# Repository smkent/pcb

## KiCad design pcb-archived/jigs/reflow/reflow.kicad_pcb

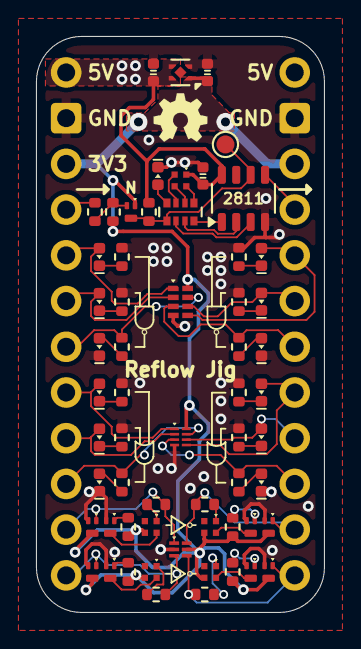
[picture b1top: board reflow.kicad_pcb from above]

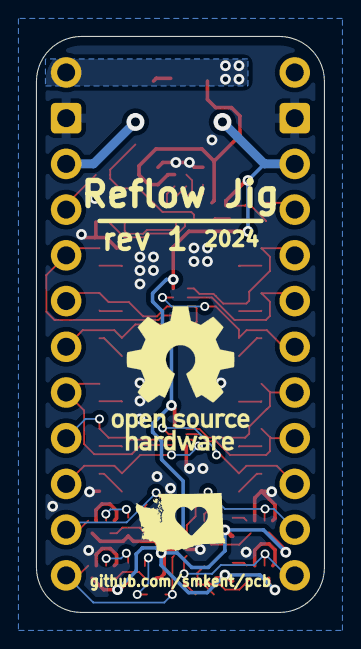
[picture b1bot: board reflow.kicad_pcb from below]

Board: 2 copper layers, 16.0 x 32.0 mm, 62 parts (2 on the bottom side), 54 nets.

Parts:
C0, C1, C2: 10u; C_0402_1005Metric
D1, D2, D3, D4, D5, D6, D7, D8, D9, D10, D11, D12, D13: Green; LED_0402_1005Metric
J1, J2: Pin headers; PinHeader_1x12_P2.54mm_Vertical_simple_pad2gnd
LED1, LED2, LED3, LED4, LED5: XL-B1010RGBT-HF; LED_RGB_XL-B1010RGBT-HF_1.0x1.0mm
Q1, Q2, Q3, Q4, Q5, Q6, Q7, Q8, Q9: SDV301N3; DFN1006-3
R1: 100R; R_0402_1005Metric
R2, R3, R4, R5, R6, R7: 10K; R_0402_1005Metric
R8, R9, R10, R11, R12, R13, R14, R15, R16, R17, R18, R19, R20, R21, R22, R23: 5K1; R_0402_1005Metric
RN1: 5K1; R_Array_Convex_4x0402
TP1: TestPoint; TestPoint_Pad_D1.0mm
U1: WS2811F; FSOP-8_3.3x1.7mm_P0.80mm
U2: 74LVC2G00HD4-7; X2-DFN2010-8_L2.0-W1.0-P0.50-BL
U3: 74LVC2G32RA3-7; X2-DFN1210-8_L1.2-W1.0-P0.30-BL
U4: 74AUP2G06FW4-7; X2-DFN1010-6_L1.0-W1.0-P0.35-BL
U5: ME6211C33U4; UDFN-4-1EP_1x1mm_P0.65mm_EP0.48x0.48mm

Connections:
+3V3: C1.1, J1.3, J2.3, LED2.3 (GK), LED3.3 (GK), LED4.3 (GK), LED5.3 (GK), Q1.1 (G), Q2.3 (D), Q4.3 (D), Q7.3 (D), Q8.3 (D), R2.2, R4.1, R5.2, R6.1, R7.2, U2.8 (V_{CC}), U3.8 (V_{CC}), U4.5 (V_{CC}), U5.1 (V_{OUT})
+5V: C0.1, C2.1, J1.1, J2.1, LED1.1 (A), R3.2, U1.8 (VDD), U5.3 (CE), U5.4 (V_{IN})
/NAND1_A_K: D1.1 (K), R14.1
/NAND1_B_K: D2.1 (K), R15.1
/NAND2_A_K: D3.1 (K), R17.1
/NAND2_B_K: D4.1 (K), R16.1
/NOT1_A_A: LED2.1 (A), R8.2
/NOT1_A_GR: Q3.1 (G), R4.2
/NOT1_A_RED: LED2.2 (RK), Q3.3 (D)
/NOT1_Y_A: LED3.1 (A), R9.1
/NOT1_Y_GR: Q5.1 (G), R5.1
/NOT1_Y_RED: LED3.2 (RK), Q5.3 (D)
/NOT2_A_A: LED4.1 (A), R11.2
/NOT2_A_GR: Q6.1 (G), R6.2
/NOT2_A_RED: LED4.2 (RK), Q6.3 (D)
/NOT2_Y_A: LED5.1 (A), R10.1
/NOT2_Y_GR: Q9.1 (G), R7.1
/NOT2_Y_RED: LED5.2 (RK), Q9.3 (D)
/OR1_A_K: D7.1 (K), R18.1
/OR1_B_K: D8.1 (K), R19.1
/OR2_A_K: D11.1 (K), R21.1
/OR2_B_K: D12.1 (K), R22.1
/WS2811_IN_3V3_F: Q1.2 (S), R1.2, R2.1
/WS2811_LED_BK: LED1.4 (BK), RN1.7 (R2.2)
/WS2811_LED_GK: LED1.3 (GK), RN1.6 (R3.2)
/WS2811_LED_RK: LED1.2 (RK), RN1.5 (R4.2)
/WS2811_OUTB: RN1.2 (R2.1), U1.3 (OUTB)
/WS2811_OUTG: RN1.3 (R3.1), U1.2 (OUTG)
/WS2811_OUTR: RN1.4 (R4.1), U1.1 (OUTR)
GND: C0.2, C1.2, C2.2, D5.1 (K), D6.1 (K), D9.1 (K), D10.1 (K), D13.1 (K), J1.2, J2.2, Q2.2 (S), Q3.2 (S), Q4.2 (S), Q5.2 (S), Q6.2 (S), Q7.2 (S), Q8.2 (S), Q9.2 (S), R14.2, R15.2, R16.2, R17.2, R18.2, R19.2, R21.2, R22.2, U1.4 (GND), U2.4 (GND), U3.4 (GND), U4.2 (GND), U5.2 (V_{SS})
NAND1_A: D1.2 (A), J1.5, U2.1 (1A)
NAND1_B: D2.2 (A), J1.6, U2.2 (1B)
NAND1_Y: J1.7, R12.1, U2.7 (1Y)
NAND2_A: D3.2 (A), J2.5, U2.5 (2A)
NAND2_B: D4.2 (A), J2.6, U2.6 (2B)
NAND2_Y: J2.7, R13.1, U2.3 (2Y)
NOT1_A: J1.11, Q2.1 (G), R8.1, U4.1 (1A)
NOT1_Y: J2.11, Q4.1 (G), R9.2, U4.6 (1Y)
NOT2_A: J1.12, Q7.1 (G), R11.1, U4.3 (2A)
NOT2_Y: J2.12, Q8.1 (G), R10.2, U4.4 (2Y)
unnamed: D5.2 (A), R12.2
unnamed: D6.2 (A), RN1.8 (R1.2)
unnamed: D9.2 (A), R20.2
unnamed: D10.2 (A), R13.2
unnamed: D13.2 (A), R23.2
OR1_A: D7.2 (A), J1.8, U3.1 (1A)
OR1_B: D8.2 (A), J1.9, U3.2 (1B)
OR1_Y: J1.10, R20.1, U3.7 (1Y)
OR2_A: D11.2 (A), J2.8, U3.5 (2A)
OR2_B: D12.2 (A), J2.9, U3.6 (2B)
OR2_Y: J2.10, R23.1, U3.3 (2Y)
WS2811_IN_3V3: J1.4, R1.1
WS2811_IN_5V: Q1.3 (D), R3.1, RN1.1 (R1.1), TP1.1, U1.6 (DIN)
WS2811_OUT_5V: J2.4, U1.5 (DO)

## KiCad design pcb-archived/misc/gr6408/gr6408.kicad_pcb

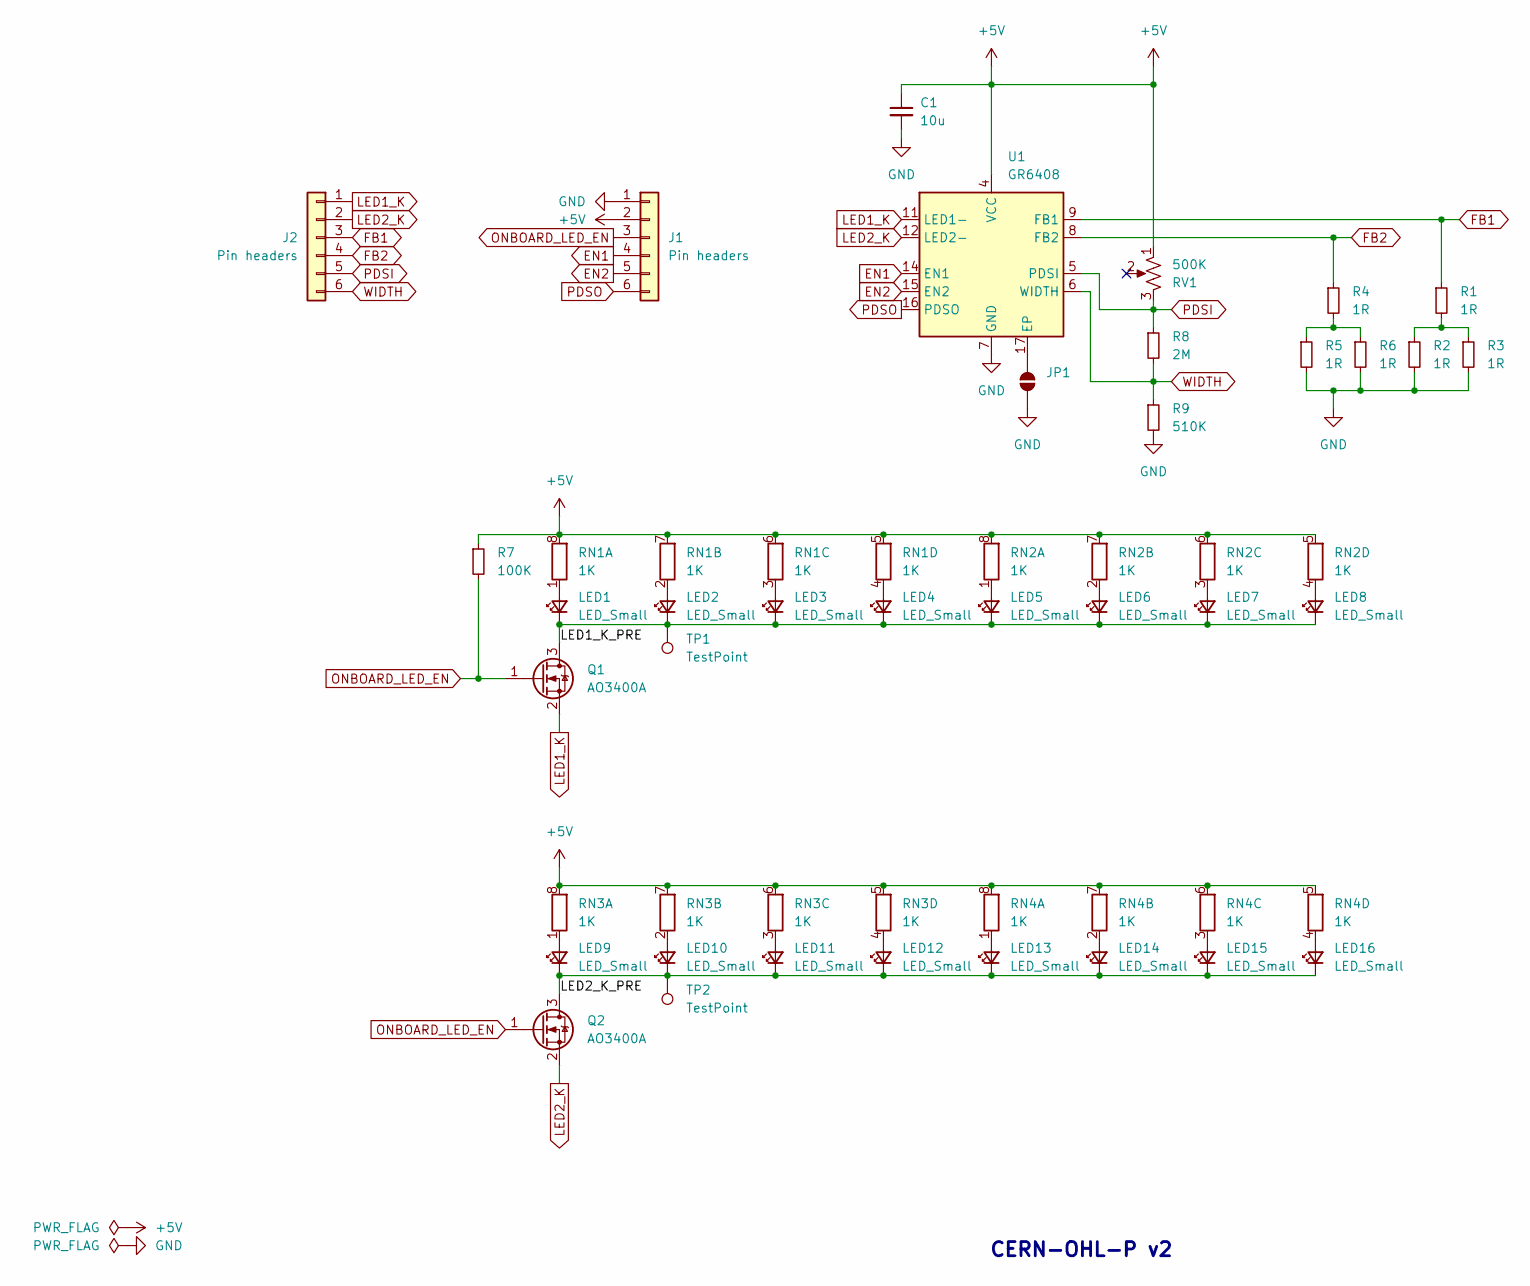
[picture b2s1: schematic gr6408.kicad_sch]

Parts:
C1: 10u; C_0603_1608Metric
J1: Pin headers; PinHeader_1x06_P2.54mm_Vertical_simple_pad1gnd
J2: Pin headers; PinHeader_1x06_P2.54mm_Vertical_simple
JP1: SolderJumper_2_Open; SolderJumper-2_P1.3mm_Open_RoundedPad1.0x1.5mm
LED1, LED2, LED3, LED4, LED5, LED6, LED7, LED8, LED9, LED10, LED11, LED12, LED13, LED14, LED15, LED16: LED_Small; LED_0402_1005Metric
Q1, Q2: AO3400A; SOT-23
R1, R2, R3, R4, R5, R6: 1R; R_0603_1608Metric
R7: 100K; R_0603_1608Metric
R8: 2M; R_0603_1608Metric
R9: 510K; R_0603_1608Metric
RN1, RN2, RN3, RN4: 1K; R_Array_Convex_4x0603
RV1: 500K; Potentiometer_3.8mmx3.0mm_Vertical
TP1, TP2: TestPoint; TestPoint_Pad_D1.0mm
U1: GR6408; QFN-16-1EP_4x4mm_P0.65mm_EP2.5x2.5mm; LCSC Part C27975231

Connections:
+5V: C1.1, J1.2, R7.1, RN1.5 (R4.2), RN1.6 (R3.2), RN1.7 (R2.2), RN1.8 (R1.2), RN2.5 (R4.2), RN2.6 (R3.2), RN2.7 (R2.2), RN2.8 (R1.2), RN3.5 (R4.2), RN3.6 (R3.2), RN3.7 (R2.2), RN3.8 (R1.2), RN4.5 (R4.2), RN4.6 (R3.2), RN4.7 (R2.2), RN4.8 (R1.2), RV1.1, U1.4 (VCC)
/LED1_K_PRE: LED1.1 (K), LED2.1 (K), LED3.1 (K), LED4.1 (K), LED5.1 (K), LED6.1 (K), LED7.1 (K), LED8.1 (K), Q1.3 (D), TP1.1
/LED2_K_PRE: LED9.1 (K), LED10.1 (K), LED11.1 (K), LED12.1 (K), LED13.1 (K), LED14.1 (K), LED15.1 (K), LED16.1 (K), Q2.3 (D), TP2.1
EN1: J1.4, U1.14 (EN1)
EN2: J1.5, U1.15 (EN2)
FB1: J2.3, R1.1, U1.9 (FB1)
FB2: J2.4, R4.1, U1.8 (FB2)
GND: C1.2, J1.1, JP1.1 (A), R2.2, R3.2, R5.2, R6.2, R9.2, U1.7 (GND)
LED1_K: J2.1, Q1.2 (S), U1.11 (LED1-)
LED2_K: J2.2, Q2.2 (S), U1.12 (LED2-)
unnamed: JP1.2 (B), U1.17 (EP)
unnamed: LED1.2 (A), RN1.1 (R1.1)
unnamed: LED2.2 (A), RN1.2 (R2.1)
unnamed: LED3.2 (A), RN1.3 (R3.1)
unnamed: LED4.2 (A), RN1.4 (R4.1)
unnamed: LED5.2 (A), RN2.1 (R1.1)
unnamed: LED6.2 (A), RN2.2 (R2.1)
unnamed: LED7.2 (A), RN2.3 (R3.1)
unnamed: LED8.2 (A), RN2.4 (R4.1)
unnamed: LED9.2 (A), RN3.1 (R1.1)
unnamed: LED10.2 (A), RN3.2 (R2.1)
unnamed: LED11.2 (A), RN3.3 (R3.1)
unnamed: LED12.2 (A), RN3.4 (R4.1)
unnamed: LED13.2 (A), RN4.1 (R1.1)
unnamed: LED14.2 (A), RN4.2 (R2.1)
unnamed: LED15.2 (A), RN4.3 (R3.1)
unnamed: LED16.2 (A), RN4.4 (R4.1)
unnamed: R1.2, R2.1, R3.1
unnamed: R4.2, R5.1, R6.1
ONBOARD_LED_EN: J1.3, Q1.1 (G), Q2.1 (G), R7.2
PDSI: J2.5, R8.1, RV1.3, U1.5 (PDSI)
PDSO: J1.6, U1.16 (PDSO)
WIDTH: J2.6, R8.2, R9.1, U1.6 (WIDTH)

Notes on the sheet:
CERN-OHL-P v2

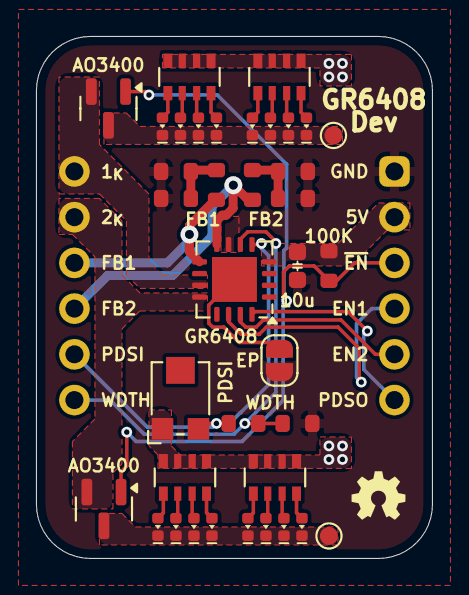
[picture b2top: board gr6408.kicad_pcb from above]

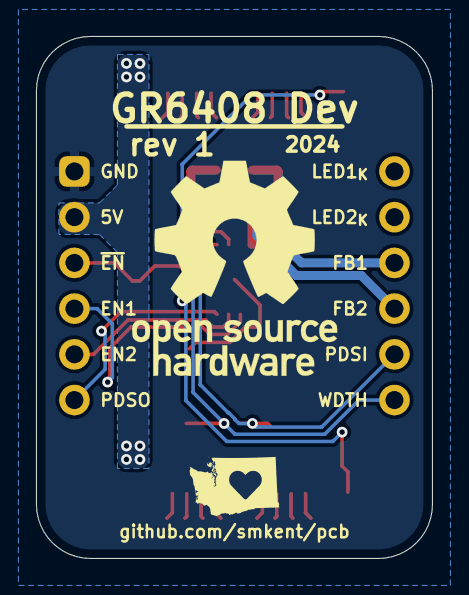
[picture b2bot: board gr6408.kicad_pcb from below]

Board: 2 copper layers, 22.0 x 29.0 mm, 39 parts (2 on the bottom side), 33 nets.

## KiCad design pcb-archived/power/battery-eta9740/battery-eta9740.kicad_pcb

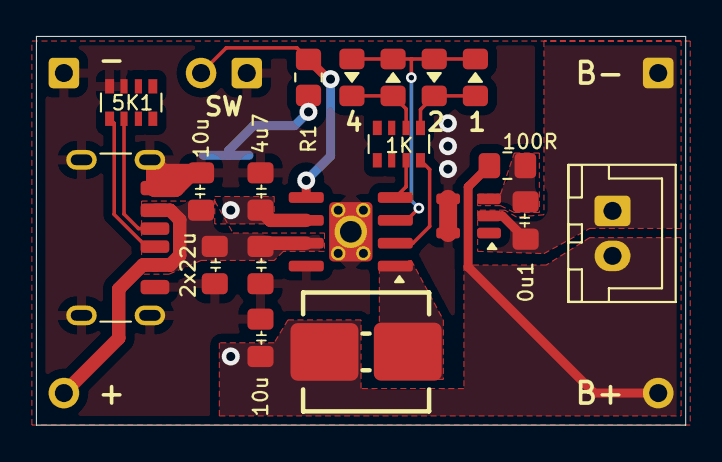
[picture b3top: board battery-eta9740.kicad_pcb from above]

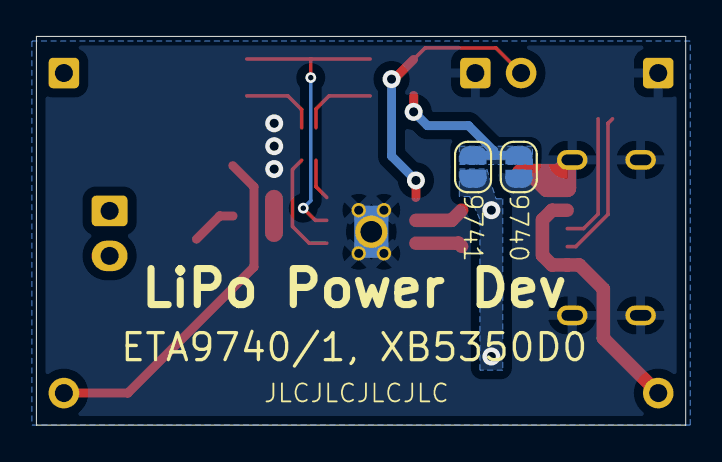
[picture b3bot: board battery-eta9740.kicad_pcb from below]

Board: 2 copper layers, 36.1 x 21.6 mm, 26 parts (2 on the bottom side), 15 nets.

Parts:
BT1: Battery_Cell; JST_XH_B2B-XH-A_1x02_P2.50mm_Vertical_simple_pad2gnd
C1: 0.1uF; C_0805_2012Metric_Pad1.18x1.45mm_HandSolder
Cbat1: 4.7uF; C_0805_2012Metric_Pad1.18x1.45mm_HandSolder
Cin1: 10uF; C_0805_2012Metric_Pad1.18x1.45mm_HandSolder
Cout1, Cout2: 22uF; C_0805_2012Metric_Pad1.18x1.45mm_HandSolder
Cusb1: 10uF; C_0805_2012Metric_Pad1.18x1.45mm_HandSolder
J0: USB_C_Receptacle_PowerOnly_6P; USB_C_Receptacle_GCT_USB4125-xx-x_6P_TopMnt_Horizontal_hand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
J1, J3: Conn_01x01; PinHeader_1x01_P2.54mm_simple
J2, J4: Conn_01x01; PinHeader_1x01_P2.54mm_simple_square
JP1, JP2: SolderJumper_2_Open; SolderJumper-2_P1.3mm_Open_RoundedPad1.0x1.5mm
L1: 22uH; Inductor_Multi_7.0x6.6_plus
LED1, LED2, LED3, LED4: LED_0805_2012Metric_Pad1.15x1.40mm_HandSolder_simple
R1: 100K; R_0805_2012Metric_Pad1.20x1.40mm_HandSolder
R2: 100R; R_0805_2012Metric_Pad1.20x1.40mm_HandSolder
RN1: R_Pack04_Split; R_Array_Convex_4x0603
RN2: 5K1; R_Array_Convex_4x0603
SW1: SW_Push; PinHeader_1x02_P2.54mm_Vertical_simple_pad2gnd
U1: ETA9740E8A; SOIC-8-1EP_3.9x4.9mm_P1.27mm_EP2.41x3.3mm_ThermalVias_Custo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
U2: XB5350D0; SOT-23-5_simple

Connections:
0/1_SEL: JP1.2 (B), JP2.1 (A), R1.1
AGND: Cbat1.1, Cin1.1, Cout1.2, Cout2.2, Cusb1.2, J0.A12 (GND), J0.B12 (GND), J0.S1 (SHIELD), J2.1, JP1.1 (A), RN2.7 (R2.2), RN2.8 (R1.2), SW1.2, U1.8 (PGND), U1.9 (AGND), U2.4 (VM), U2.5 (VM)
B+: BT1.1 (+), Cbat1.2, Cin1.2, J3.1, JP2.2 (B), L1.1, R2.1, U1.6 (BAT)
B-: BT1.2 (-), C1.1, J4.1, U2.2 (GND)
BATVDD: C1.2, R2.2, U2.3 (VDD)
ISET: R1.2, SW1.1, U1.5 (ISET)
LED1: RN1.4 (R4.1), U1.2 (LED1)
LED2: LED1.1 (K), LED2.2 (A), LED3.1 (K), LED4.2 (A), U1.3 (LED2)
LED3: RN1.3 (R3.1), U1.4 (LED3)
unnamed: J0.A5 (CC1), RN2.2 (R2.1)
unnamed: J0.B5 (CC2), RN2.1 (R1.1)
unnamed: LED1.2 (A), LED2.1 (K), RN1.5 (R4.2)
unnamed: LED3.2 (A), LED4.1 (K), RN1.6 (R3.2)
SW: L1.2, U1.1 (SW)
VCC: Cout1.1, Cout2.1, Cusb1.1, J0.A9 (VBUS), J0.B9 (VBUS), J1.1, U1.7 (OUT)

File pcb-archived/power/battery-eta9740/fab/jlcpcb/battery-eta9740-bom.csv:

Comment,Designator,Footprint,LCSC
~,"LED1,LED2,LED3,LED4",custom:LED_0805_2012Metric_Pad1.15x1.40mm_HandSolder_simple,
22uH,L1,custom:Inductor_Multi_7.0x6.6_plus,C5832376
100K,R1,Resistor_SMD:R_0805_2012Metric_Pad1.20x1.40mm_HandSolder,C17379
R_Pack04_Split,RN1,Resistor_SMD:R_Array_Convex_4x0603,
Conn_01x01,"J2,J4",custom:PinHeader_1x01_P2.54mm_simple_square,
SW_Push,SW1,custom:PinHeader_1x02_P2.54mm_Vertical_simple_pad2gnd,
XB5350D0,U2,custom:SOT-23-5_simple,C2760002
Battery_Cell,BT1,custom:JST_XH_B2B-XH-A_1x02_P2.50mm_Vertical_simple_pad2gnd,
22uF,"Cout1,Cout2",custom:C_0805_2012Metric_Pad1.18x1.45mm_HandSolder,
ETA9740E8A,U1,custom:SOIC-8-1EP_3.9x4.9mm_P1.27mm_EP2.41x3.3mm_ThermalVias_CustomVias_Large,C7465512
10uF,"Cin1,Cusb1",custom:C_0805_2012Metric_Pad1.18x1.45mm_HandSolder,
USB_C_Receptacle_PowerOnly_6P,J0,custom:USB_C_Receptacle_GCT_USB4125-xx-x_6P_TopMnt_Horizontal_handsolder,
4.7uF,Cbat1,custom:C_0805_2012Metric_Pad1.18x1.45mm_HandSolder,
Conn_01x01,"J1,J3",custom:PinHeader_1x01_P2.54mm_simple,
0.1uF,C1,custom:C_0805_2012Metric_Pad1.18x1.45mm_HandSolder,C1525
100R,R2,Resistor_SMD:R_0805_2012Metric_Pad1.20x1.40mm_HandSolder,
5K1,RN2,Resistor_SMD:R_Array_Convex_4x0603,

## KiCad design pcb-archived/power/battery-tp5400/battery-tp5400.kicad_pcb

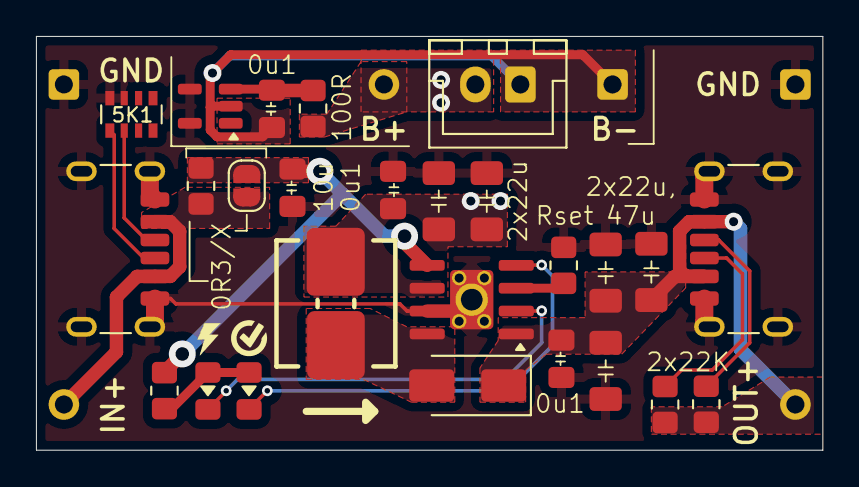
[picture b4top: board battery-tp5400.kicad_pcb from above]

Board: 2 copper layers, 43.7 x 23.0 mm, 32 parts (0 on the bottom side), 16 nets.

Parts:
BT1: Battery_Cell; JST_XH_B2B-XH-A_1x02_P2.50mm_Vertical_simple_pad2gnd
C0: 0.1uF; C_0805_2012Metric_Pad1.18x1.45mm_HandSolder
C1: 10u; C_0805_2012Metric_Pad1.18x1.45mm_HandSolder
C2, C5: 0u1; C_0805_2012Metric_Pad1.18x1.45mm_HandSolder
C3, C4, C6, C7: 22u; C_1206_3216Metric_Pad1.33x1.80mm_HandSolder
C8: 47u; C_1206_3216Metric_Pad1.33x1.80mm_HandSolder
D3: SS34; D_SMA
J0, J7: USB_C_Receptacle_PowerOnly_6P; USB_C_Receptacle_GCT_USB4125-xx-x_6P_TopMnt_Horizontal_hand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
J1, J3, J5: Conn_01x01; PinHeader_1x01_P2.54mm_simple
J2, J4, J6: Conn_01x01; PinHeader_1x01_P2.54mm_simple_square
JP1: SolderJumper_2_Open; SolderJumper-2_P1.3mm_Open_RoundedPad1.0x1.5mm
L2: 10u; Inductor_Multi_7.0x6.6_plus
LED1, LED2: LED; LED_0805_2012Metric_Pad1.15x1.40mm_HandSolder_simple
R0: 0R3; R_0805_2012Metric_Pad1.20x1.40mm_HandSolder
R1: 1K; R_0805_2012Metric_Pad1.20x1.40mm_HandSolder
R2: 100R; R_0805_2012Metric_Pad1.20x1.40mm_HandSolder
R3: 1K1; R_0805_2012Metric_Pad1.20x1.40mm_HandSolder
R4, R5: 22K; R_0805_2012Metric_Pad1.20x1.40mm_HandSolder
RN1: 5K1; R_Array_Convex_4x0603
U1: TP5400_C2891434; SOIC-8-1EP_3.9x4.9mm_P1.27mm_EP2.41x3.3mm_ThermalVias_Custo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
U2: XB5350D0; SOT-23-5_simple

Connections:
B+: BT1.1 (+), C2.2, C3.2, C4.2, J3.1, L2.2, R2.1, U1.6 (BAT)
B-: BT1.2 (-), C0.1, J4.1, U2.2 (GND)
BATVDD: C0.2, R2.2, U2.3 (VDD)
GND: C1.1, C2.1, C3.1, C4.1, C5.1, C6.1, C7.1, C8.1, J0.A12 (GND), J0.B12 (GND), J0.S1 (SHIELD), J2.1, J6.1, J7.A12 (GND), J7.B12 (GND), J7.S1 (SHIELD), R3.1, RN1.7 (R2.2), RN1.8 (R1.2), U1.7 (GND), U1.9 (EP), U2.4 (VM), U2.5 (VM)
LED1: LED1.1 (K), U1.2 (~CHRG)
LED2: LED2.1 (K), U1.4 (~STDBY)
LX: D3.2 (A), L2.1, U1.8 (LX)
unnamed: J0.A5 (CC1), RN1.2 (R2.1)
unnamed: J0.B5 (CC2), RN1.1 (R1.1)
unnamed: J7.A5 (CC1), R4.2
unnamed: J7.B5 (CC2), R5.2
unnamed: LED1.2 (A), LED2.2 (A), R1.2
unnamed: R3.2, U1.3 (PROG)
VCC: J0.A9 (VBUS), J0.B9 (VBUS), J1.1, JP1.2 (B), R0.2
VIN: C1.2, JP1.1 (A), R0.1, R1.1, U1.5 (VCC)
VOUT: C5.2, C6.2, C7.2, C8.2, D3.1 (K), J5.1, J7.A9 (VBUS), J7.B9 (VBUS), R4.1, R5.1, U1.1 (VOUT)

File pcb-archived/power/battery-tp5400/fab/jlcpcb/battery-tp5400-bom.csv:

Comment,Designator,Footprint,LCSC
LED,"LED1,LED2",custom:LED_0805_2012Metric_Pad1.15x1.40mm_HandSolder_simple,
22u,"C3,C4,C6,C7",custom:C_1206_3216Metric_Pad1.33x1.80mm_HandSolder,
0u1,"C2,C5",custom:C_0805_2012Metric_Pad1.18x1.45mm_HandSolder,
10u,C1,custom:C_0805_2012Metric_Pad1.18x1.45mm_HandSolder,
Conn_01x01,"J2,J4,J6",custom:PinHeader_1x01_P2.54mm_simple_square,
1K,R1,Resistor_SMD:R_0805_2012Metric_Pad1.20x1.40mm_HandSolder,
22K,R5,Resistor_SMD:R_0805_2012Metric_Pad1.20x1.40mm_HandSolder,C25768
47u,C8,custom:C_1206_3216Metric_Pad1.33x1.80mm_HandSolder,
XB5350D0,U2,custom:SOT-23-5_simple,C2760002
Battery_Cell,BT1,custom:JST_XH_B2B-XH-A_1x02_P2.50mm_Vertical_simple_pad2gnd,
5K1,RN1,Resistor_SMD:R_Array_Convex_4x0603,
TP5400_C2891434,U1,custom:SOIC-8-1EP_3.9x4.9mm_P1.27mm_EP2.41x3.3mm_ThermalVias_CustomVias_Large,C2891434
0R3,R0,Resistor_SMD:R_0805_2012Metric_Pad1.20x1.40mm_HandSolder,
Conn_01x01,"J1,J3,J5",custom:PinHeader_1x01_P2.54mm_simple,
USB_C_Receptacle_PowerOnly_6P,J0,custom:USB_C_Receptacle_GCT_USB4125-xx-x_6P_TopMnt_Horizontal_handsolder,
22K,R4,Resistor_SMD:R_0805_2012Metric_Pad1.20x1.40mm_HandSolder,
USB_C_Receptacle_PowerOnly_6P,J7,custom:USB_C_Receptacle_GCT_USB4125-xx-x_6P_TopMnt_Horizontal_handsolder,
1K1,R3,Resistor_SMD:R_0805_2012Metric_Pad1.20x1.40mm_HandSolder,
0.1uF,C0,custom:C_0805_2012Metric_Pad1.18x1.45mm_HandSolder,C1525
100R,R2,Resistor_SMD:R_0805_2012Metric_Pad1.20x1.40mm_HandSolder,
10u,L2,custom:Inductor_Multi_7.0x6.6_plus,
SS34,D3,Diode_SMD:D_SMA,

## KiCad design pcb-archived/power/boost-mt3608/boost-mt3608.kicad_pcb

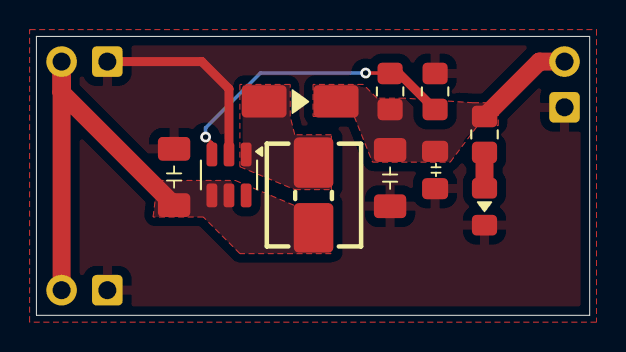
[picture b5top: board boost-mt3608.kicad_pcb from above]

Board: 2 copper layers, 30.7 x 15.5 mm, 13 parts (0 on the bottom side), 6 nets.

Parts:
C1: 22uF; C_1206_3216Metric_Pad1.33x1.80mm_HandSolder
C2: 22uf; C_1206_3216Metric_Pad1.33x1.80mm_HandSolder
C3: 10uF; C_0805_2012Metric_Pad1.18x1.45mm_HandSolder
D1: SS34; D_SMA_simple
J1, J2, J3: Conn_01x02; PinHeader_1x02_P2.54mm_Vertical_simple_pad2gnd
L1: 22uH; Inductor_Multi_5.2x5.7_2x2.5
LED1: Boost; LED_0805_2012Metric_Pad1.15x1.40mm_HandSolder_simple
R1: 75K; R_0805_2012Metric_Pad1.20x1.40mm_HandSolder
R2, R3: 10K; R_0805_2012Metric_Pad1.20x1.40mm_HandSolder
U1: MT3608; SOT-23-6

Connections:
FB: R1.2, R2.1, U1.3 (FB)
GND: C1.2, C2.2, C3.2, J1.2, J2.2, J3.2, LED1.1 (K), R2.2, U1.2 (GND)
unnamed: LED1.2 (A), R3.2
SW: D1.2 (A), L1.2, U1.1 (SW)
VCC: C1.1, J1.1, J2.1, L1.1, U1.4 (EN), U1.5 (IN)
VOUT: C2.1, C3.1, D1.1 (K), J3.1, R1.1, R3.1

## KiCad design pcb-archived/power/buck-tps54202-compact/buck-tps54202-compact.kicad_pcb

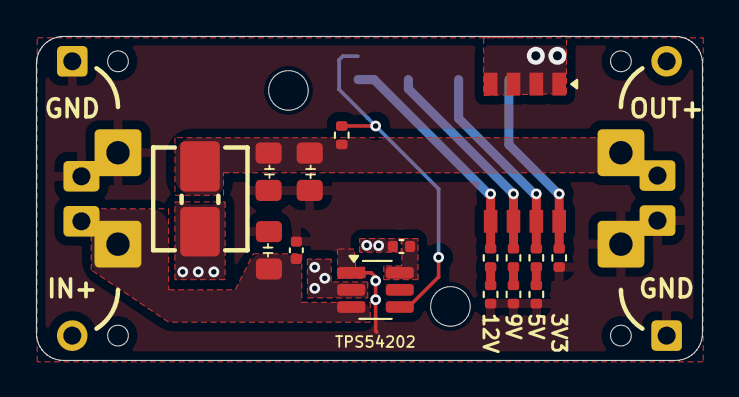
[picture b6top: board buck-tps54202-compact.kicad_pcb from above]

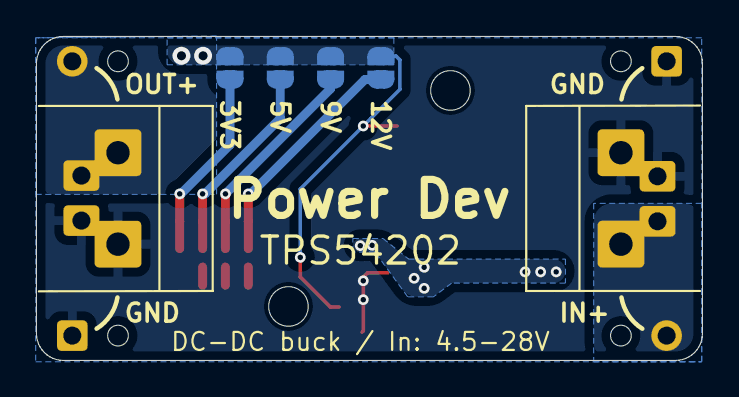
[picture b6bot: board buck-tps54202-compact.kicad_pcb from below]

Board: 2 copper layers, 37.0 x 18.0 mm, 26 parts (10 on the bottom side), 13 nets.

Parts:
C1: 10u; C_0805_2012Metric_Pad1.18x1.45mm_HandSolder
C2, C3: 0u1; C_0402_1005Metric
C4, C5: 22u; C_0805_2012Metric_Pad1.18x1.45mm_HandSolder
J1, J3: Conn_01x03; PinHeader_1x01_P2.54mm_simple
J2, J4: Conn_01x03; PinHeader_1x01_P2.54mm_simple_square
J5, J6: Screw_Terminal_01x02; TerminalBlock_or_JST_2.54_1x02
JP1, JP2, JP3, JP4: SolderJumper_2_Open; SolderJumper-2_P1.3mm_Open_RoundedPad1.0x1.5mm_simple
L1: 15u; Inductor_Multi_5.2x5.7_2x2.5
R1: 100K; R_0402_1005Metric
R2: 22K; R_0402_1005Metric
R3: 12K; R_0402_1005Metric
R4: 1K2; R_0402_1005Metric
R5: 6.8K; R_0402_1005Metric
R6: 220R; R_0402_1005Metric
R7: 5.1K; R_0402_1005Metric
R8: 120R; R_0402_1005Metric
SW1: SW_DIP_x04; SW_DIP_SPSTx04_Slide_P1.27mm_simple
U1: TPS54202DDCR; SOT-23-6_Handsoldering

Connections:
3V3_SELECT: JP1.1 (A), R2.1, SW1.8
5V_SELECT: JP2.1 (A), R3.1, SW1.7
9V_SELECT: JP3.1 (A), R5.1, SW1.6
12V_SELECT: JP4.1 (A), R7.1, SW1.5
BOOT: C3.1, U1.6 (BOOT)
FB: JP1.2 (B), JP2.2 (B), JP3.2 (B), JP4.2 (B), R1.2, SW1.1, SW1.2, SW1.3, SW1.4, U1.4 (FB)
GND: C1.2, C2.2, C4.2, C5.2, J2.1, J4.1, J5.2, J6.2, R2.2, R4.2, R6.2, R8.2, U1.1 (GND)
unnamed: R3.2, R4.1
unnamed: R5.2, R6.1
unnamed: R7.2, R8.1
SW: C3.2, L1.1, U1.2 (SW)
VIN: C1.1, C2.1, J1.1, J5.1, U1.3 (VIN)
VOUT: C4.1, C5.1, J3.1, J6.1, L1.2, R1.1

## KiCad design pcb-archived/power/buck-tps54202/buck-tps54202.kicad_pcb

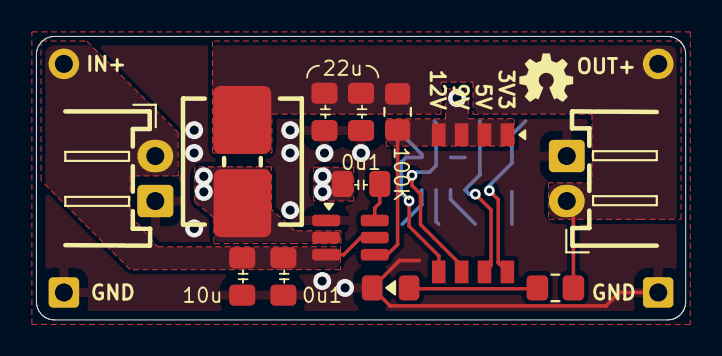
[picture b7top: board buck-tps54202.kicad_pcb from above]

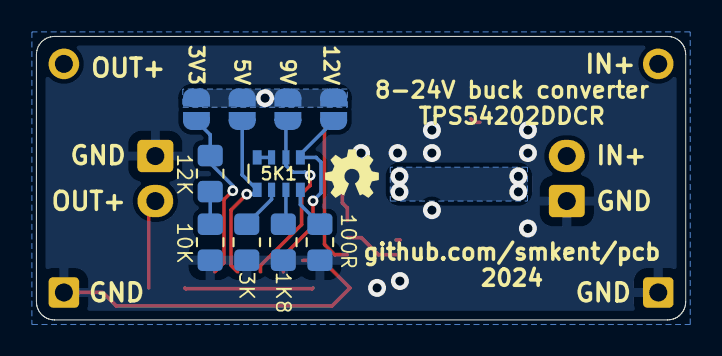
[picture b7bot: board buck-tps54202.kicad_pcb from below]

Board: 2 copper layers, 36.1 x 15.7 mm, 27 parts (14 on the bottom side), 16 nets.

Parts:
C1: 10u; C_0805_2012Metric_Pad1.18x1.45mm_HandSolder
C2, C3: 0u1; C_0805_2012Metric_Pad1.18x1.45mm_HandSolder
C4, C5: 22u; C_0805_2012Metric_Pad1.18x1.45mm_HandSolder
D1: LED; LED_0805_2012Metric_Pad1.15x1.40mm_HandSolder_simple
J1, J3: Conn_01x03; PinHeader_1x01_P2.54mm_simple
J2, J4: Conn_01x03; PinHeader_1x01_P2.54mm_simple_square
J5, J6: Conn_01x02; JST_XH_S2B-XH-2AW_1x02_P2.50mm_pad2gnd_trim2
JP1, JP2, JP3, JP4: SolderJumper_2_Open; SolderJumper-2_P1.3mm_Open_RoundedPad1.0x1.5mm_simple
L1: 15u; Inductor_Multi_7.0x6.6_plus
R0: 100K; R_0805_2012Metric_Pad1.20x1.40mm_HandSolder
R1: 10K; R_0805_2012Metric_Pad1.20x1.40mm_HandSolder
R2: 12K; R_0805_2012Metric_Pad1.20x1.40mm_HandSolder
R4: 3K; R_0805_2012Metric_Pad1.20x1.40mm_HandSolder
R6: 1K8; R_0805_2012Metric_Pad1.20x1.40mm_HandSolder
R8: 100R; R_0805_2012Metric_Pad1.20x1.40mm_HandSolder
R10: 1K; R_0805_2012Metric_Pad1.20x1.40mm_HandSolder
RN1: 5K1; R_Array_Convex_4x0603
SW1: SW_DIP_x04; SW_DIP_SPSTx04_Slide_P1.27mm_simple
U1: TPS54202DDCR; SOT-23-6_Handsoldering_simple

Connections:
3V3_SELECT: JP1.1 (A), R2.1, SW1.8
5V_SELECT: JP2.1 (A), RN1.5 (R4.2), SW1.7
9V_SELECT: JP3.1 (A), RN1.2 (R2.1), SW1.6
12V_SELECT: JP4.1 (A), RN1.1 (R1.1), SW1.5
BOOT: C3.1, U1.6 (BOOT)
FB: JP1.2 (B), JP2.2 (B), JP3.2 (B), JP4.2 (B), R0.2, SW1.1, SW1.2, SW1.3, SW1.4, U1.4 (FB)
GND: C1.2, C2.2, C4.2, C5.2, D1.1 (K), J2.1, J4.1, J5.2, J6.2, R1.2, R4.2, R6.2, R8.2, U1.1 (GND)
unnamed: D1.2 (A), R10.2
unnamed: R1.1, R2.2
unnamed: R8.1, RN1.8 (R1.2)
unnamed: R6.1, RN1.7 (R2.2)
unnamed: RN1.3 (R3.1), RN1.4 (R4.1)
unnamed: R4.1, RN1.6 (R3.2)
SW: C3.2, L1.1, U1.2 (SW)
VIN: C1.1, C2.1, J1.1, J5.1, U1.3 (VIN), U1.5 (EN)
VOUT: C4.1, C5.1, J3.1, J6.1, L1.2, R0.1, R10.1

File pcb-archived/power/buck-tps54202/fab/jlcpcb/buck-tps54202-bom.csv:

Comment,Designator,Footprint,LCSC
Conn_01x03,"J1,J3",custom:PinHeader_1x01_P2.54mm_simple,
100K,R0,Resistor_SMD:R_0805_2012Metric_Pad1.20x1.40mm_HandSolder,
3K,R4,Resistor_SMD:R_0805_2012Metric_Pad1.20x1.40mm_HandSolder,
22u,"C4,C5",custom:C_0805_2012Metric_Pad1.18x1.45mm_HandSolder,C45783
Conn_01x02,"J5,J6",custom:JST_XH_S2B-XH-2AW_1x02_P2.50mm_pad2gnd_trim2,
SW_DIP_x04,SW1,custom:SW_DIP_SPSTx04_Slide_P1.27mm_simple,
10K,R1,Resistor_SMD:R_0805_2012Metric_Pad1.20x1.40mm_HandSolder,
10u,C1,custom:C_0805_2012Metric_Pad1.18x1.45mm_HandSolder,C440198
Conn_01x03,"J2,J4",custom:PinHeader_1x01_P2.54mm_simple_square,
100R,R8,Resistor_SMD:R_0805_2012Metric_Pad1.20x1.40mm_HandSolder,
TPS54202DDCR,U1,custom:SOT-23-6_Handsoldering_simple,C191884
5K1,RN1,Resistor_SMD:R_Array_Convex_4x0603,
15u,L1,custom:Inductor_Multi_7.0x6.6_plus,
0u1,"C2,C3",custom:C_0805_2012Metric_Pad1.18x1.45mm_HandSolder,
12K,R2,Resistor_SMD:R_0805_2012Metric_Pad1.20x1.40mm_HandSolder,
1K,R10,Resistor_SMD:R_0805_2012Metric_Pad1.20x1.40mm_HandSolder,
LED,D1,custom:LED_0805_2012Metric_Pad1.15x1.40mm_HandSolder_simple,
1K8,R6,Resistor_SMD:R_0805_2012Metric_Pad1.20x1.40mm_HandSolder,

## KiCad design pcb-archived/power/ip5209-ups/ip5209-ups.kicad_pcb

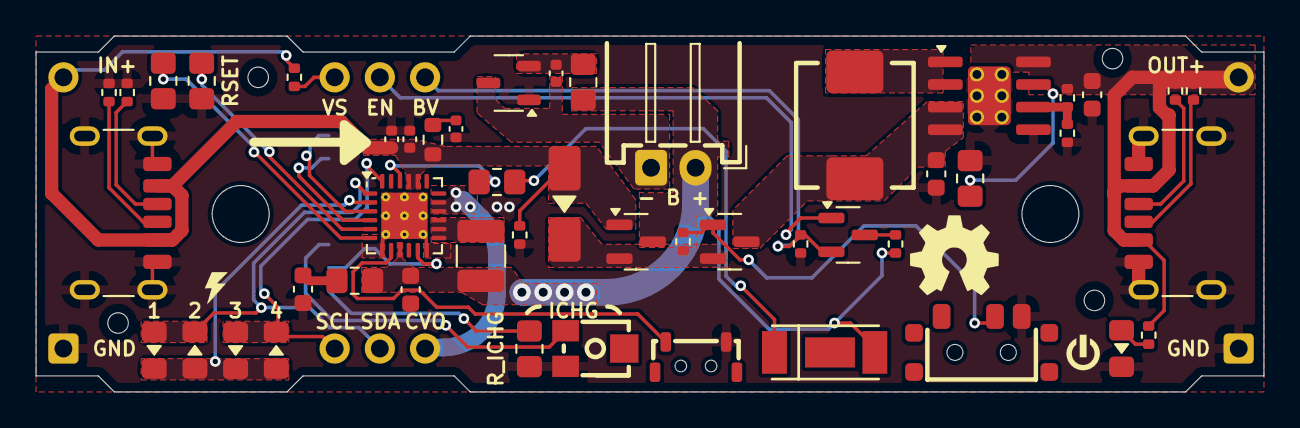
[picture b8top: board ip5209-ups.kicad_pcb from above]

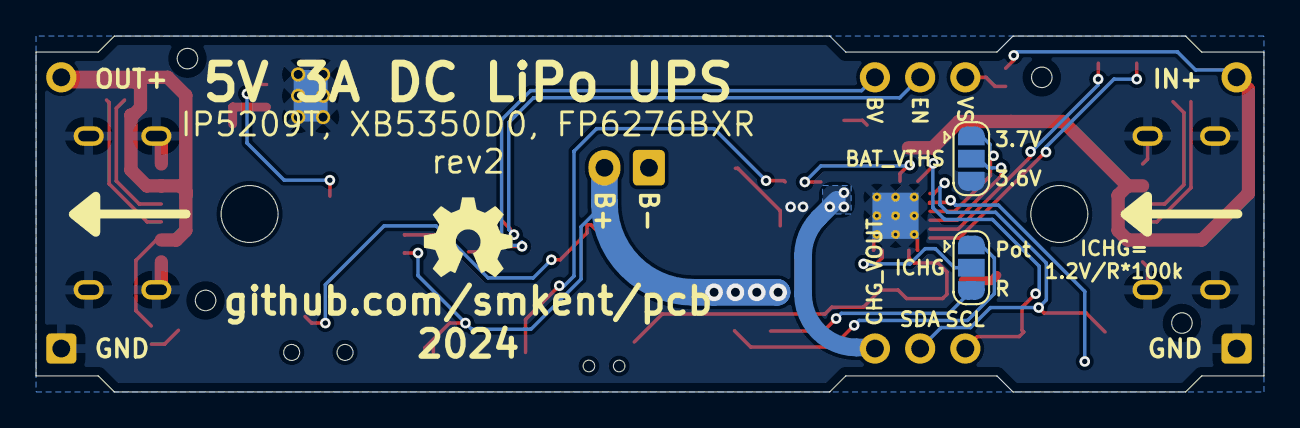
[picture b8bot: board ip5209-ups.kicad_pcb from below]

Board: 2 copper layers, 69.0 x 20.0 mm, 57 parts (8 on the bottom side), 38 nets.

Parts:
BT1: Battery_Cell; JST_XH_S2B-XH-2AW_1x02_P2.50mm_pad2gnd_trim
C1, C6: 10uF; C_0402_1005Metric
C2, C7, C10, C11: 22uF; C_0603_1608Metric
C3: 100nF; C_0402_1005Metric
C9: 0.1uF; C_0402_1005Metric
D1: SS34; D_SMA_simple
J1, J2: USB_C_Receptacle_PowerOnly_6P; USB_C_Receptacle_GCT_USB4125-xx-x_6P_TopMnt_Horizontal_hand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
J3, J9: Conn_01x03; PinHeader_1x03_P2.54mm_Vertical_simple
J5, J8: Conn_01x01; PinHeader_1x01_P2.54mm_simple
J11, J12: Conn_01x01; PinHeader_1x01_P2.54mm_simple_square
JP1, JP2: SolderJumper_3_Open; SolderJumper-3_P1.3mm_Open_RoundedPad1.0x1.5mm
L1: 1uH; L_1210_3225Metric
L2: 4.7uH; IND-SMD_L7.0-W6.6
LED1, LED2, LED3, LED4: LED_0805_2012Metric_Pad1.15x1.40mm_HandSolder_simple
LED5: LED-SMD_3P-L5.7-W3.0-RD
LED6: Boost; LED_0805_2012Metric_Pad1.15x1.40mm_HandSolder_simple
Q1, Q2: AO3401A; SOT-23
Q3: BSS138; SOT-23
R1: 120K; R_0805_2012Metric_Pad1.20x1.40mm_HandSolder
R2: 20R; R_0805_2012Metric_Pad1.20x1.40mm_HandSolder
R3: 2R; R_0603_1608Metric
R4: 0R5; R_0805_2012Metric_Pad1.20x1.40mm_HandSolder
R5: 100R; R_0805_2012Metric_Pad1.20x1.40mm_HandSolder
R6, R7, R9, R10, R13, R14, R15, R16, R17: 10K; R_0402_1005Metric
R8: 75K; R_0402_1005Metric
R11, R12: 5K1; R_0402_1005Metric
R18: 10K; R_0805_2012Metric_Pad1.20x1.40mm_HandSolder
R19: 47K; R_0805_2012Metric_Pad1.20x1.40mm_HandSolder
R20: 0R; R_0805_2012Metric_Pad1.20x1.40mm_HandSolder
RV1: R_Potentiometer_US; RES-ADJ-SMD_VG039NCH
SW1: SW_Push; SW-SMD_BZCN_TSA002A35XXX
SW2: SW_SPDT; SW-SMD_3P-P1.50_L2.7-W6.6
U1: IP5209T; QFN-24-1EP_4x4mm_P0.5mm_EP2.6x2.6mm_ThermalVias
U2: XB3306D; SOT-23-3
U3: FP6276BXR-G1; SOIC-8-1EP_3.9x4.9mm_P1.27mm_EP2.41x3.3mm_ThermalVias_Custo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

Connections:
B+: BT1.1 (+), C2.1, L1.2, LED5.2 (A), Q1.3 (D), R4.1, R5.1, R15.1, U1.9 (BAT)
B-: BT1.2 (-), C9.1, U2.3 (GND)
BATVDD: C9.2, R5.2, U2.2 (VDD)
BAT_SENSE: J9.1, Q3.2 (S), R16.1
BAT_SENSE_ENABLE: J9.2, Q3.1 (G)
BOOST: C10.1, L2.1, Q2.3 (D), U3.3 (VIN), U3.4 (EN)
BOOST_OC: R19.2, U3.7 (OC)
BOOST_SW: L2.2, U3.1 (LX), U3.2 (LX)
CHARGE_VOUT: J3.3, U1.16 (VOUT), U1.17 (VOUT)
FB: R8.2, R9.1, U3.6 (FB)
GND: C1.2, C2.2, C3.2, C6.2, C7.2, C10.2, C11.2, J1.A12 (GND), J1.B12 (GND), J1.S1 (SHIELD), J2.A12 (GND), J2.B12 (GND), J2.S1 (SHIELD), J11.1, J12.1, JP1.3 (B), LED6.1 (K), R1.2, R6.2, R9.2, R11.2, R12.2, R16.2, R18.2, R19.1, R20.1, RV1.3, SW1.1, SW2.3 (C), U1.7 (AGND), U1.12 (PGND), U1.25 (EP), U2.1 (VM), U3.5 (GND), U3.9 (EP)
ICHG: JP2.2 (C), U1.11 (ICHG)
KEY: SW1.2, U1.8 (KEY)
LED1: J3.1, LED3.2 (A), LED4.1 (K), U1.24 (L1)
LED2: J3.2, LED1.2 (A), LED2.1 (K), U1.1 (L2)
LED3: LED1.1 (K), LED2.2 (A), LED3.1 (K), LED4.2 (A), U1.2 (L3)
LIGHT: R2.1, U1.22 (LIGHT)
LOAD_SWITCH: D1.1 (K), Q1.2 (S), Q2.2 (S), R7.1
unnamed: C6.1, R3.2
unnamed: C7.1, R4.2
unnamed: J1.A5 (CC1), R12.1
unnamed: J1.B5 (CC2), R11.1
unnamed: J2.A5 (CC1), R13.2
unnamed: J2.B5 (CC2), R14.2
unnamed: JP2.1 (A), RV1.1
unnamed: JP2.3 (B), R1.1
unnamed: LED5.1 (K), R2.2
unnamed: LED6.2 (A), R10.2
unnamed: Q2.1 (G), R7.2, SW2.2 (B)
unnamed: Q3.3 (D), R15.2
unnamed: R20.2, U1.6 (NTC)
POWER_IN_SENSE: J9.3, R17.2
RSET: R18.1, U1.5 (RSET)
SW: L1.1, U1.13 (LX), U1.14 (LX), U1.15 (LX)
VIN: C1.1, C3.1, D1.2 (A), J1.A9 (VBUS), J1.B9 (VBUS), J5.1, Q1.1 (G), R3.1, R6.1, R17.1, U1.20 (VIN), U1.21 (VIN)
VOUT: C11.1, J2.A9 (VBUS), J2.B9 (VBUS), J8.1, R8.1, R10.1, R13.1, R14.1, U3.8 (VO)
VREG: JP1.1 (A), U1.3 (VREG)
VTHS: JP1.2 (C), U1.4 (VTHS)

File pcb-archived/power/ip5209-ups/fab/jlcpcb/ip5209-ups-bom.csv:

Comment,Designator,Footprint,LCSC
10K,"R6,R7,R9,R10,R13,R14,R15,R16,R17",Resistor_SMD:R_0402_1005Metric,C25744
Battery_Cell,BT1,custom:JST_XH_S2B-XH-2AW_1x02_P2.50mm_pad2gnd_trim,
Boost,LED6,custom:LED_0805_2012Metric_Pad1.15x1.40mm_HandSolder_simple,
BSS138,Q3,Package_TO_SOT_SMD:SOT-23,C7420339
2R,R3,Resistor_SMD:R_0603_1608Metric,C22977
120K,R1,Resistor_SMD:R_0805_2012Metric_Pad1.20x1.40mm_HandSolder,C17436
~,"LED1,LED2,LED3,LED4",custom:LED_0805_2012Metric_Pad1.15x1.40mm_HandSolder_simple,
22uF,"C2,C7,C10,C11",Capacitor_SMD:C_0603_1608Metric,C59461
R_Potentiometer_US,RV1,lcsc:RES-ADJ-SMD_VG039NCH,
IP5209T,U1,Package_DFN_QFN:QFN-24-1EP_4x4mm_P0.5mm_EP2.6x2.6mm_ThermalVias,C284964
10uF,"C1,C6",Capacitor_SMD:C_0402_1005Metric,C15525
20R,R2,Resistor_SMD:R_0805_2012Metric_Pad1.20x1.40mm_HandSolder,C17544
0R,R20,Resistor_SMD:R_0805_2012Metric_Pad1.20x1.40mm_HandSolder,C17477
100nF,C3,Capacitor_SMD:C_0402_1005Metric,C307331
SW_Push,SW1,lcsc:SW-SMD_BZCN_TSA002A35XXX,
1uH,L1,Inductor_SMD:L_1210_3225Metric,C3002559
Conn_01x03,"J3,J9",custom:PinHeader_1x03_P2.54mm_Vertical_simple,
0R5,R4,Resistor_SMD:R_0805_2012Metric_Pad1.20x1.40mm_HandSolder,
~,LED5,lcsc:LED-SMD_3P-L5.7-W3.0-RD,
10K,R18,Resistor_SMD:R_0805_2012Metric_Pad1.20x1.40mm_HandSolder,
100R,R5,Resistor_SMD:R_0805_2012Metric_Pad1.20x1.40mm_HandSolder,C17408
0.1uF,C9,Capacitor_SMD:C_0402_1005Metric,C1525
XB3306D,U2,Package_TO_SOT_SMD:SOT-23-3,C2759992
AO3401A,"Q1,Q2",Package_TO_SOT_SMD:SOT-23,C15127
SW_SPDT,SW2,lcsc:SW-SMD_3P-P1.50_L2.7-W6.6,C2998803
SS34,D1,custom:D_SMA_simple,C8678
4.7uH,L2,lcsc:IND-SMD_L7.0-W6.6,C5307631
75K,R8,Resistor_SMD:R_0402_1005Metric,C25798
47K,R19,Resistor_SMD:R_0805_2012Metric_Pad1.20x1.40mm_HandSolder,C17713
FP6276BXR-G1,U3,custom:SOIC-8-1EP_3.9x4.9mm_P1.27mm_EP2.41x3.3mm_ThermalVias_CustomVias,C82652
USB_C_Receptacle_PowerOnly_6P,J1,custom:USB_C_Receptacle_GCT_USB4125-xx-x_6P_TopMnt_Horizontal_handsolder,
Conn_01x01,"J11,J12",custom:PinHeader_1x01_P2.54mm_simple_square,
5K1,"R11,R12",Resistor_SMD:R_0402_1005Metric,C25905
USB_C_Receptacle_PowerOnly_6P,J2,custom:USB_C_Receptacle_GCT_USB4125-xx-x_6P_TopMnt_Horizontal_handsolder,
Conn_01x01,"J5,J8",custom:PinHeader_1x01_P2.54mm_simple,
